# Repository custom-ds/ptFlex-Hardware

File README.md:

# Project: Traveler ptFlex
Following the sunsetting of the PTMini project, the ptFlex is the second generation of the ArduinoTrack APRS tracker.  

The ptFlex is based on the same ATMega processor and much of the same hardware as the ArduinoTrack, but a newer and smaller form factor.  The new form factor removes the larger Arduino Shield connectors that proved to be fragile and rarely used.  Instead, the digial pins have been replaced with a single "Qwiic" connector, conforming to Sparkfun's Qwiic standards.

[Sparkfun Qwiic Connector Standard](https://www.sparkfun.com/qwiic)

Board version 1.0.3 is release-candidate level, and is currently undergoing flight testing.

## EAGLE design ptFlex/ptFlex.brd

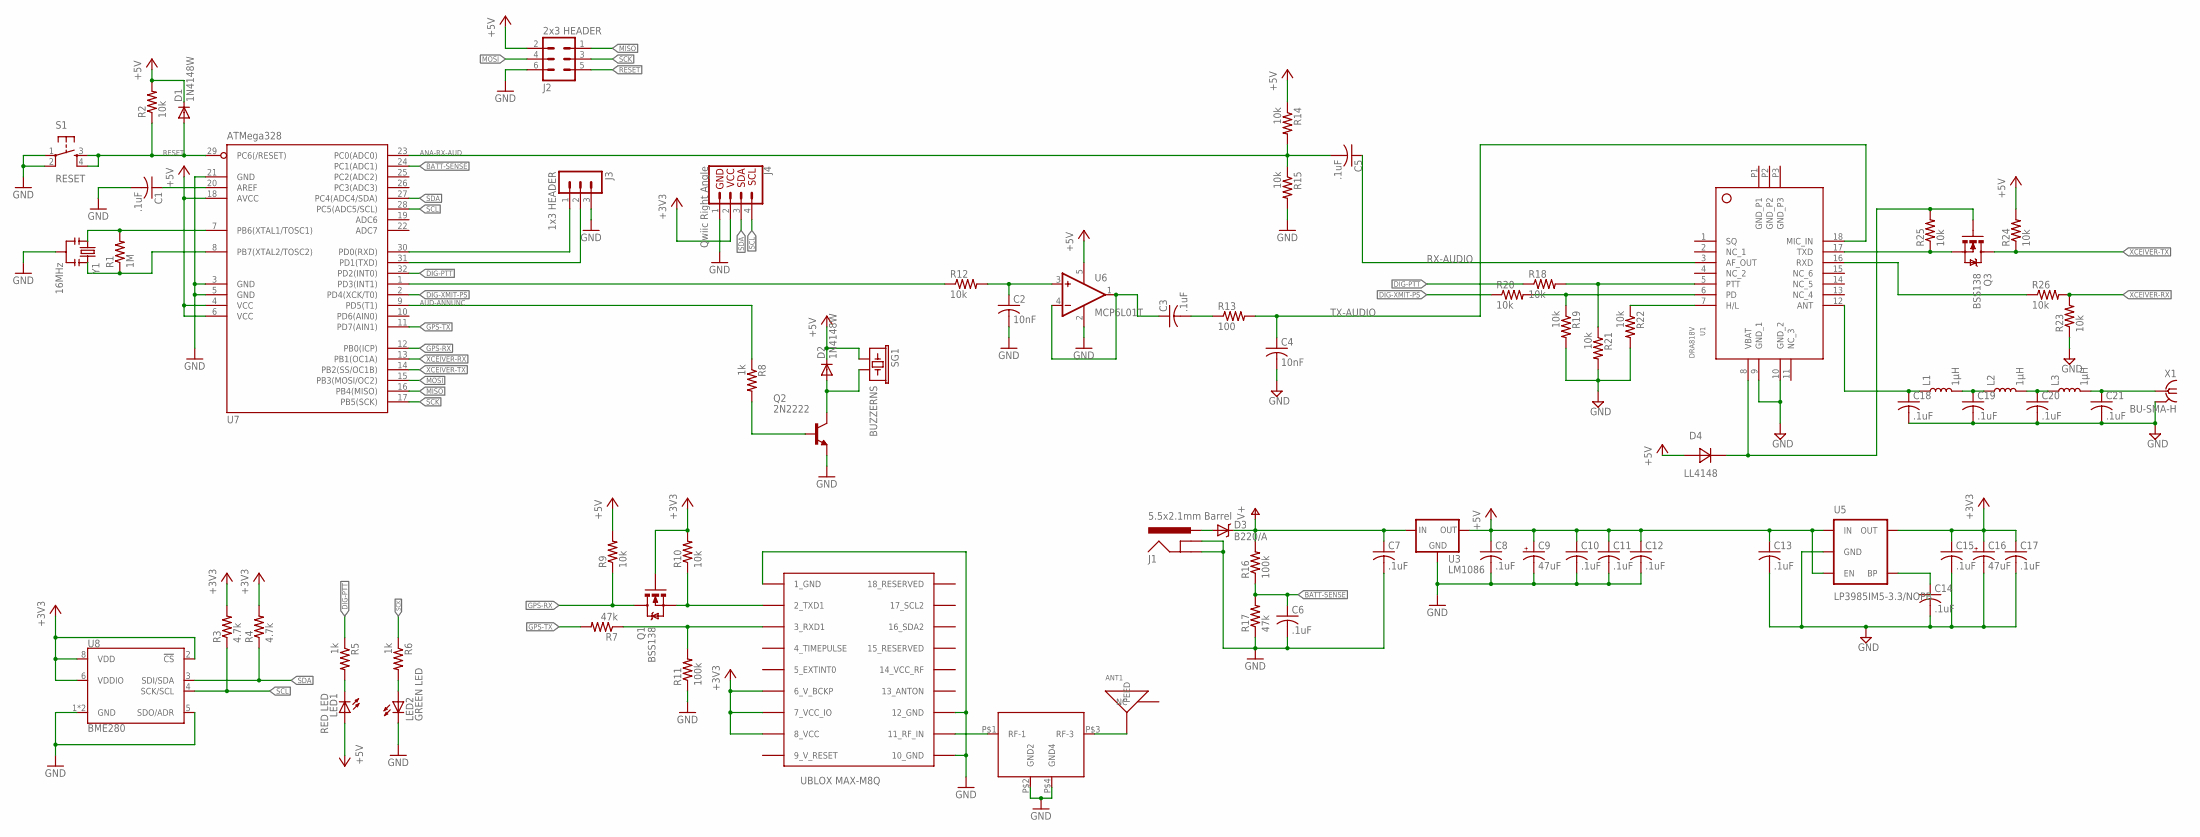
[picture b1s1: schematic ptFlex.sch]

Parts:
ANT1: GPS ANTENNA; 1575AT43A40; DIGIKEY 712-1003-1-ND
C1, C3, C5, C6, C7, C8, C10, C11, C12, C13, C14, C15, C17, C18, C19, C20, C21: .1uF; C0805; DIGIKEY 311-1361-1-ND
C2, C4: 10nF; C0805; DIGIKEY 399-1158-1-ND
C9, C16: 47uF; 153CLV-0605; DIGIKEY PCE3842CT-ND
D1, D2: 1N4148W; SOD123; DIGIKEY 1N4148W-FDICT-ND
D3: B220/A; SMA-DIODE; DIGIKEY 641-1258-1-ND
D4: LL4148; SOD-80
F1: MURATA-GPS-FILTER; DIGIKEY 583-1198-1-ND
J1: 5.5x2.1mm Barrel; POWER_JACK_SMD; DIGIKEY CP-002AHPJCT-ND
J2: 2x3 HEADER; MA03-2; DIGIKEY 952-2121-ND
J3: 1x3 HEADER; MA03-1; DIGIKEY 952-2264-ND
J4: Qwiic Right Angle; 1X04_1MM_RA; DIGIKEY 455-1804-1-ND
L1, L2, L3: 1µH; L0805
LED1: RED LED; CHIPLED_1206; DIGIKEY 160-1405-1-ND
LED2: GREEN LED; CHIPLED_1206; DIGIKEY 160-1169-1-ND
Q1, Q3: BSS138; SOT23; DIGIKEY BSS138KCT-ND
Q2: 2N2222; SOT23-BEC; DIGIKEY MMBT2222AFSCT-ND
R1: 1M; R0805; DIGIKEY 311-1.0MARCT-ND
R2, R9, R10, R12, R14, R15, R18, R19, R20, R21, R22, R23, R24, R25, R26: 10k; R0805; DIGIKEY 311-10.0KCRCT-ND
R3, R4: 4.7k; R0805; DIGIKEY 311-4.7KARCT-ND
R5, R6, R8: 1k; R0805; DIGIKEY 311-1.0KARCT-ND
R7, R17: 47k; R0805; DIGIKEY 311-47.0KCRCT-ND
R11, R16: 100k; R0805; DIGIKEY 311-100KCRCT-ND
R13: 100; R0805; DIGIKEY 311-100ARCT-ND
S1: RESET; TACTILE_SWITCH_SMD; DIGIKEY CKN9104CT-ND
SG1: BUZZERNS; BUZZER-12MM-NS; DIGIKEY 102-1155-ND
U1: DRA818V; SMD_DRA818
U2: UBLOX_MAX; DIGIKEY 672-1003-1-ND
U3: LM1086; TO263; DIGIKEY LM1086ISX-5.0/NOPBCT-ND
U5: LP3985IM5-3.3/NOPB; SOT23-5; DIGIKEY LP3985IM5-3.3/NOPBCT-ND
U6: MCP6L01T; SOT23-5; DIGIKEY MCP6L01T-E/OTCT-ND
U7: ATMega328; TQFP32-08; DIGIKEY ATMEGA328P-AU-ND
U8: BME280; LGA-8-2.5X2.5; DIGIKEY 828-1063-1-ND
X1: BU-SMA-H; DIGIKEY CONSMA001-ND
Y1: 16MHz; RESONATOR-SMD; DIGIKEY 478-5420-1-ND

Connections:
9_V_RESET: U2.9_V_RESET
+3V3: C15.1, C16.+, C17.1, J4.2, Q1.1 (G), R3.2, R4.2, R10.2, U2.6_V_BCKP, U2.7_VCC_IO, U2.8_VCC, U5.5 (OUT), U8.2 (!CS), U8.6 (VDDIO), U8.8 (VDD)
+5V: C8.1, C9.+, C10.1, C11.1, C12.1, C13.1, D1.C, D2.C, D4.ANODE, J2.2, LED1.A, R2.2, R9.2, R14.1, R24.2, SG1.+ (1), U3.2 (OUT), U5.1 (IN), U5.3 (EN), U6.5 (V+), U7.4 (VCC), U7.6 (VCC), U7.18 (AVCC)
ANA-RX-AUD: C5.2, R14.2, R15.1, U7.23 (PC0(ADC0))
AUD-ANNUNC: R8.1, U7.9 (PD5(T1))
BATT-SENSE: C6.1, R16.1, R17.2, U7.24 (PC1(ADC1))
DIG-PTT: R5.1, R18.1, U7.32 (PD2(INT0))
DIG-XMIT-PS: R20.1, U7.2 (PD4(XCK/T0))
GND: C1.2, C2.2, C4.2, C6.2, C7.2, C8.2, C9.-, C10.2, C11.2, C12.2, C13.2, C14.2, C15.2, C16.-, C17.2, C18.2, C19.2, C20.2, C21.2, F1.P$2 (GND2), F1.P$4 (GND4), J1.GND (GNDBREAK), J1.P$4 (GND), J2.6, J3.3, J4.1, LED2.C, Q2.E, R11.1, R15.2, R17.1, R19.2, R21.2, R22.2, R23.1, S1.1, S1.2, U1.9 (GND_1), U1.10 (GND_2), U2.1_GND, U2.10_GND, U2.12_GND, U3.1 (GND), U5.2 (GND), U6.2 (V-), U7.3 (GND), U7.5 (GND), U7.21 (GND), U8.1 (GND), U8.5 (SDO/ADR), U8.7 (GND), X1.2, X1.3 (2), X1.4 (2), X1.5 (2), Y1.2
GPS-RX: Q1.3 (D), R9.1, U7.12 (PB0(ICP))
GPS-TX: R7.2, U7.11 (PD7(AIN1))
MISO: J2.1, U7.16 (PB4(MISO))
MOSI: J2.4, U7.15 (PB3(MOSI/OC2))
unnamed: C2.1, R12.2, U6.3 (+IN)
unnamed: F1.P$1 (RF-1), U2.11_RF_IN
unnamed: ANT1.FEED, F1.P$3 (RF-3)
unnamed: C20.1, L2.2, L3.1
unnamed: C19.1, L1.2, L2.1
unnamed: C18.1, L1.1, U1.12 (ANT)
unnamed: C21.1, L3.2, X1.1
unnamed: D3.A, J1.VIN0 (PWR)
unnamed: D2.A, Q2.C, SG1.- (2)
unnamed: C4.1, R13.2, U1.18 (MIC_IN)
unnamed: C3.1, U6.1 (OUT), U6.4 (-IN)
unnamed: D4.CATHODE, Q3.1 (G), R25.2, U1.8 (VBAT)
unnamed: R12.1, U7.1 (PD3(INT1))
unnamed: R18.2, R21.1, U1.5 (PTT)
unnamed: Q1.2 (S), R10.1, U2.2_TXD1
unnamed: R19.1, R20.2, U1.6 (PD)
unnamed: R1.1, U7.8 (PB7(XTAL2/TOSC2)), Y1.3
unnamed: R7.1, R11.2, U2.3_RXD1
unnamed: R22.1, U1.7 (H/L)
unnamed: Q3.2 (S), R25.1, U1.17 (TXD)
unnamed: LED1.C, R5.2
unnamed: LED2.A, R6.2
unnamed: Q2.B, R8.2
unnamed: R26.1, U1.16 (RXD)
unnamed: C1.1, U7.20 (AREF)
unnamed: C14.1, U5.4 (BP)
unnamed: R1.2, U7.7 (PB6(XTAL1/TOSC1)), Y1.1
RESET: D1.A, J2.5, R2.1, S1.3, S1.4, U7.29 (PC6(/RESET))
RX-AUDIO: C5.1, U1.3 (AF_OUT)
RXD: J3.1, U7.30 (PD0(RXD))
SCK: J2.3, R6.1, U7.17 (PB5(SCK))
SCL: J4.4, R3.1, U7.28 (PC5(ADC5/SCL)), U8.4 (SCK/SCL)
SDA: J4.3, R4.1, U7.27 (PC4(ADC4/SDA)), U8.3 (SDI/SDA)
TX-AUDIO: C3.2, R13.1
TXD: J3.2, U7.31 (PD1(TXD))
V+: C7.1, D3.C, R16.2, U3.3 (IN)
XCEIVER-RX: R23.2, R26.2, U7.13 (PB1(OC1A))
XCEIVER-TX: Q3.3 (D), R24.1, U7.14 (PB2(SS/OC1B))

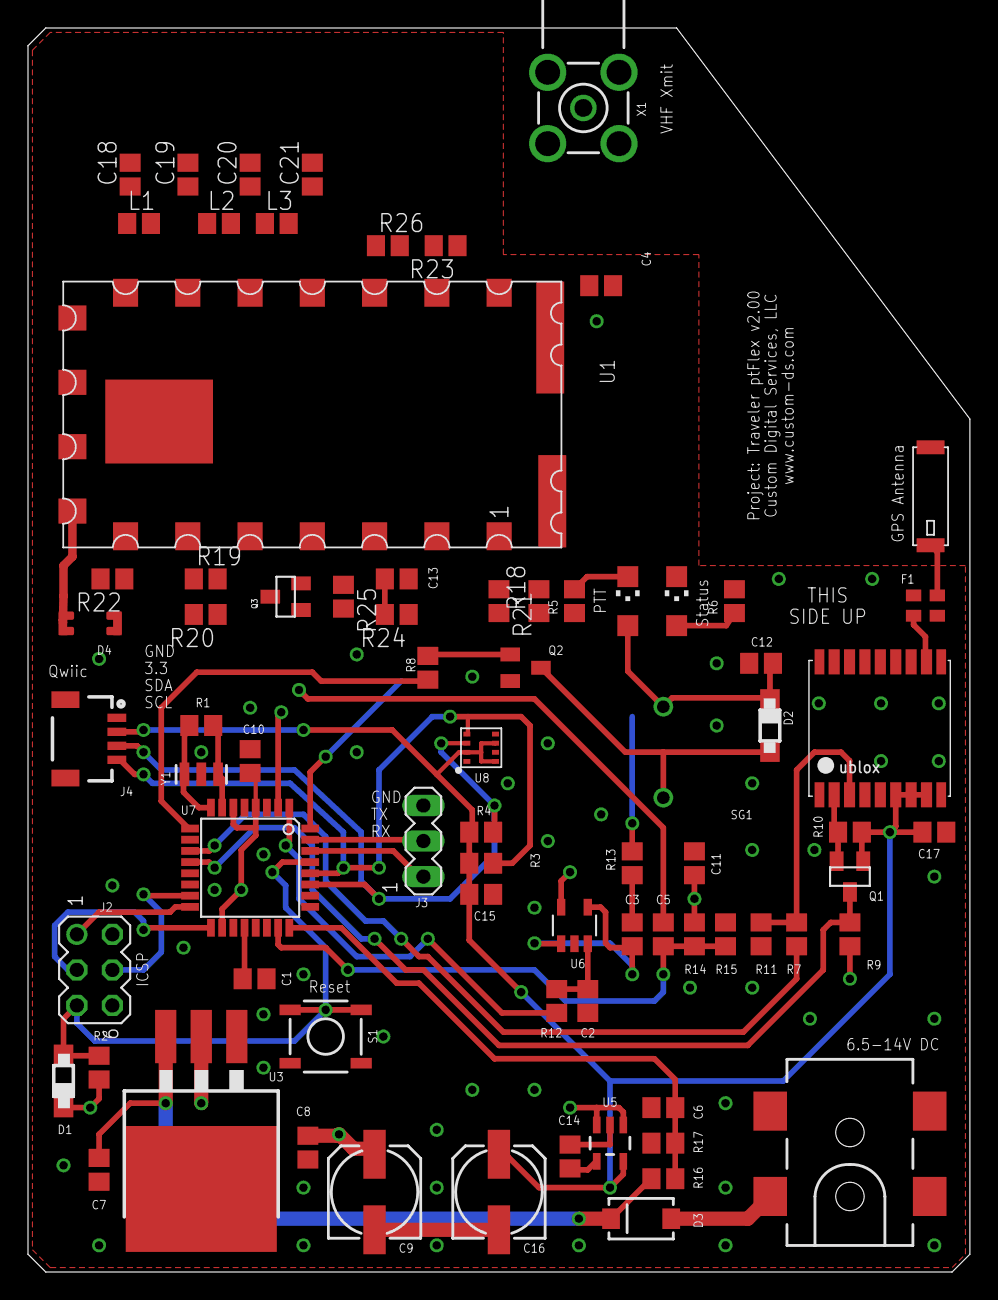
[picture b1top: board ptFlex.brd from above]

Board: 4 copper layers, 67.3 x 88.9 mm, 76 parts (0 on the bottom side), 50 nets.

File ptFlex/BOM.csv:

"Qty";"Value";"Device";"Package";"Parts";"Description";"ALT-PART";"DIGIKEY";"MF";"MPN";"OC_FARNELL";"OC_NEWARK";"PROD_ID";"SF_ID";"VALUE";
"13";".1uF";"C-USC0805";"C0805";"C1, C3, C5, C6, C7, C8, C10, C11, C12, C13, C14, C15, C17";"CAPACITOR, American symbol";"";"311-1361-1-ND";"";"";"";"";"";"";"";
"1";"100";"R-US_R0805";"R0805";"R13";"RESISTOR, American symbol";"";"311-100ARCT-ND";"";"";"";"";"";"";"";
"2";"100k";"R-US_R0805";"R0805";"R11, R16";"RESISTOR, American symbol";"";"311-100KCRCT-ND";"";"";"";"";"";"";"";
"6";"10k";"R-US_R0805";"R0805";"R2, R9, R10, R12, R14, R15";"RESISTOR, American symbol";"";"311-10.0KCRCT-ND";"";"";"";"";"";"";"";
"2";"10nF";"C-USC0805";"C0805";"C2, C4";"CAPACITOR, American symbol";"";"399-1158-1-ND";"";"";"";"";"";"";"";
"7";"160 ohm";"SM-1206";"SM-1206";"L1, L2, L3, L4, L5, L6, L7";"INDUCTOR";"";"240-2411-1-ND";"";"";"unknown";"unknown";"";"";"";
"1";"16MHz";"RESONATOR16MHZ";"RESONATOR-SMD";"Y1";"Resonator";"";"478-5420-1-ND";"";"";"";"";"XTAL-08900";"";"16MHz";
"1";"1M";"R-US_R0805";"R0805";"R1";"RESISTOR, American symbol";"";"311-1.0MARCT-ND";"";"";"";"";"";"";"";
"2";"1N4148W";"DIODE-SOD123";"SOD123";"D1, D2";"DIODE";"";"1N4148W-FDICT-ND";"";"";"";"";"";"";"";
"3";"1k";"R-US_R0805";"R0805";"R5, R6, R8";"RESISTOR, American symbol";"";"311-1.0KARCT-ND";"";"";"";"";"";"";"";
"1";"1x3 HEADER";"MA03-1";"MA03-1";"SV1";"PIN HEADER";"";"952-2264-ND";"";"";"unknown";"unknown";"";"";"";
"1";"2N2222";"BC817-16LT1SMD";"SOT23-BEC";"Q2";"NPN Transistor";"";"MMBT2222AFSCT-ND";"";"";"";"";"";"";"";
"1";"2x3 HEADER";"MA03-2";"MA03-2";"SV3";"PIN HEADER";"";"952-2121-ND";"";"";"unknown";"unknown";"";"";"";
"2";"4.7k";"R-US_R0805";"R0805";"R3, R4";"RESISTOR, American symbol";"";"311-4.7KARCT-ND";"";"";"";"";"";"";"";
"2";"47k";"R-US_R0805";"R0805";"R7, R17";"RESISTOR, American symbol";"";"311-47.0KCRCT-ND";"";"";"";"";"";"";"";
"2";"47uF";"CPOL-US153CLV-0605";"153CLV-0605";"C9, C16";"POLARIZED CAPACITOR, American symbol";"";"PCE3842CT-ND";"";"";"";"";"";"";"";
"1";"5.5x2.1mm Barrel";"POWER_JACKSMD";"POWER_JACK_SMD";"J1";"Power Jack Connector";"";"CP-002AHPJCT-ND";"";"";"";"";"CONN-08106";"PRT-12748";"5.5x2.1mm Barrel";
"1";"ATMega328";"MEGA8-AI";"TQFP32-08";"U7";"MICROCONTROLLER";"";"ATMEGA328P-AU-ND";"";"ATMEGA8-16AU";"9171371";"73M8863";"";"";"";
"1";"B220/A";"B340A";"SMA-DIODE";"D3";"Schottky Diode";"";"641-1258-1-ND";"";"";"";"";"DIO-09886";"";"BA340A";
"1";"BME280";"BME280";"LGA-8-2.5X2.5";"U8";"Bosch BME280 &ndash; Combined Humidity and Pressure Sensor";"";"";"";"";"";"";"IC-13090";"";"BME280";
"1";"BSS138";"MOSFET-NCHANNELBSS138";"SOT23";"Q1";"Common NMOSFET Parts";"";"BSS138KCT-ND";"";"";"";"";"TRANS-00830";"";"";
"1";"BU-SMA-H";"BU-SMA-H";"BU-SMA-H";"X1";"FEMALE SMA CONNECTOR";"";"CONSMA001-ND";"";"";"unknown";"unknown";"";"";"";
"1";"BUZZERNS";"BUZZERNS";"BUZZER-12MM-NS";"SG1";"Buzzer 12mm";"";"102-1155-ND";"";"";"";"";"";"";"";
"1";"GPS ANTENNA";"GPS_ANT_SMDBAR";"1575AT43A40";"ANT1";"1.575 GHz GPS Antenna Johanson Technology";"";"712-1003-1-ND";"";"";"";"";"";"";"";
"1";"GREEN LED";"LEDCHIPLED_1206";"CHIPLED_1206";"LED2";"LED";"";"160-1169-1-ND";"";"";"";"";"";"";"";
"1";"LM1086";"LM1086TO263";"TO263";"U3";"";"";"LM1086ISX-5.0/NOPBCT-ND";"";"";"";"";"";"";"";
"1";"LP3985IM5-3.3/NOPB";"V_REG_LDOSMD";"SOT23-5";"U5";"Voltage Regulator LDO";"";"LP3985IM5-3.3/NOPBCT-ND";"";"";"";"";"";"";"";
"1";"MCP6L01T";"OPA725DBV";"SOT23-5";"U6";"Very Low Noise, High-Speed, 12V CMOS Operational Amplifier";"";"MCP6L01T-E/OTCT-ND";"";"";"";"";"";"";"";
"1";"Qwiic Right Angle";"I2C_STANDARDQWIIC";"1X04_1MM_RA";"SV2";"SparkFun I2C Standard Pinout Header";"";"";"";"";"";"";"CONN-13694";"";"Qwiic Right Angle";
"1";"RADIOMETRIX-HX1-CUSTOM";"RADIOMETRIX-HX1-CUSTOM";"RADIOMETRIX-HX1-CUSTOM";"U4";"";"";"";"";"";"";"";"";"";"";
"1";"RED LED";"LEDCHIPLED_1206";"CHIPLED_1206";"LED1";"LED";"";"160-1405-1-ND";"";"";"";"";"";"";"";
"1";"RESET";"TAC_SWITCHSMD";"TACTILE_SWITCH_SMD";"S1";"Momentary Switch";"";"CKN9104CT-ND";"";"";"";"";"SWCH-08247";"";"";
"1";"UBLOX_MAX";"UBLOX_MAX";"UBLOX_MAX";"U2";"UBLOX MAX";"UBLOX MAX-M8Q";"672-1003-1-ND";"";"";"";"";"";"";"";

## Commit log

2018-02-23 Initial commit of the second generation tracker
2018-12-25 Check In for Flex 1.0.1
    Final fab-ready board for 1.0.1.
2018-12-26 Fixed alignment for transmitter board
    Shifted piezo down, and SMA up to make room for transmitter board.
2018-12-26 Version 1.0.2 Final commit
    Generated Gerber files and sent to production house.
2018-12-28 Updating readme.
2019-01-20 Rebranding to ptFlex
    Changed name, moved piezo slightly down on board to increase clearance. Updated to 1.03.
    Reorganized assembly instructions to provide assembly details.
2019-01-20 More rebranding changes.
2019-01-23 Added digikey part numbers to missing parts.
2019-04-14 Added GPS filter
    Version 1.04
2019-05-26 Gerbers for 1.0.4
2019-07-13 Minor tweak to piezo to open up ground plane
2021-05-26 Final for version 1.02
    Switching to version 2.0 which does away with backwards compatibility for the RadioMetrix modules.
2025-06-15 Final check in for hardware version 1

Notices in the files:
parts and their libraries:
SparkFun-FreqCtrl: Licensing: CC v3.0 Share-Alike You are welcome to use this library for commercial purposes.
SparkFun-Sensors: Licensing: Creative Commons ShareAlike 4.0 International - https://creativecommons.org/licenses/by-sa/4.0
